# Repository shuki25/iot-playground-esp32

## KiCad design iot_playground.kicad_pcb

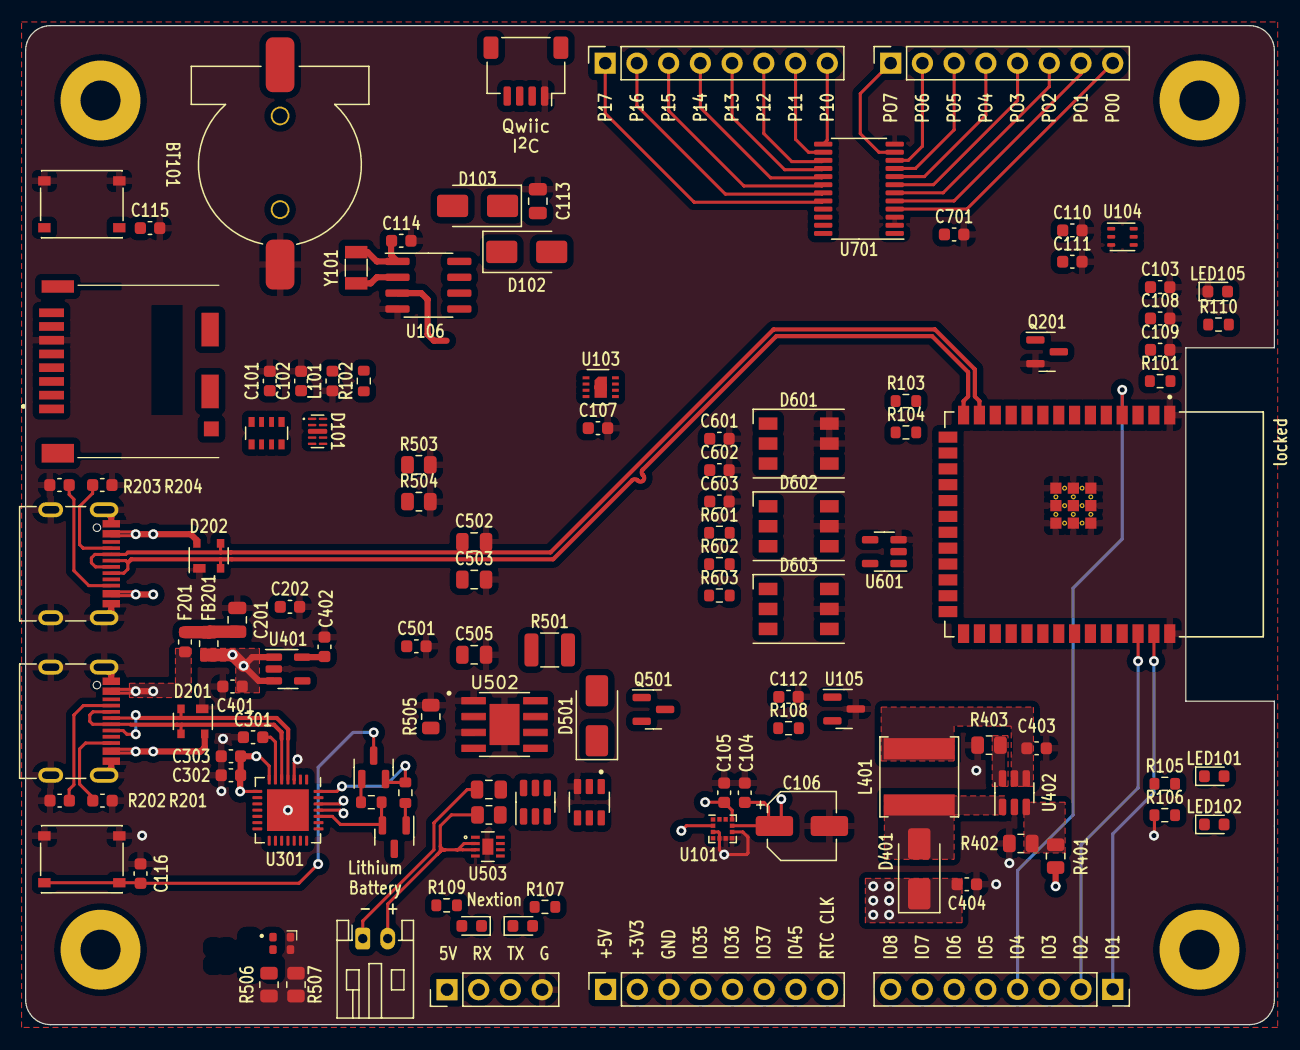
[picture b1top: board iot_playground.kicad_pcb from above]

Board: 4 copper layers, 100.0 x 80.0 mm, 121 parts (0 on the bottom side), 104 nets.

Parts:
BT101: Battery_Cell; BatteryHolder_CR1220
C101, C108: 10uF; C_0603_1608Metric
C102, C104, C105, C107, C109, C110, C112, C115, C116, C202, C301, C303, C601, C602, C603, C701: 100nF; C_0603_1608Metric
C103, C302: 1uF; C_0603_1608Metric
C106: 10uF; CP_Elec_5x5.4
C111, C402: 4.7uF; C_0603_1608Metric
C113, C504, C505: 100nF; C_0805_2012Metric
C114: 15pF; C_0603_1608Metric
C201, C502, C503: 10uF; C_0805_2012Metric
C401, C403, C404, C501: 22uF; C_0603_1608Metric
D101: RClamp0524PATCT; SLP2510P8
D102, D103, D401, D501: D_Schottky; D_SMA
D201, D202: SP0503BAHT; SOT-143
D601, D602, D603: WS2813B; LED_WS2812_PLCC6_5.0x5.0mm_P1.6mm
F201: Polyfuse_Small; Fuse_0603_1608Metric
FB201: FerriteBead_Small; R_0805_2012Metric
H101, H102, H103, H104: MountingHole_Pad; MountingHole_3.2mm_M3_Pad
J101: Micro_SD_Card_Det_Hirose_DM3CS-SF; DM3CS-SF
J102: Conn_01x04; PinHeader_1x04_P2.54mm_Vertical
J103: Conn_01x04; JST_SH_SM04B-SRSS-TB_1x04-1MP_P1.00mm_Horizontal
J104, J106, J701, J702: Conn_01x08; PinSocket_1x08_P2.54mm_Vertical
J105: Conn_01x02; JST_PH_S2B-PH-K_1x02_P2.00mm_Horizontal
J201, J202: USB_C_Receptacle_USB2.0; USB_C_Receptable_918-418K2023S40001
L101: L_Ferrite_Small; L_0603_1608Metric
L401: 6.8 uH; L_6.0x6.0_H4.5
LED101, LED103: BLUE; LED_0603_1608Metric
LED102, LED104: GREEN; LED_0603_1608Metric
LED105: RED; LED_0603_1608Metric
LED501: LED_RAGB; LED-4_1.6x1.6x0.85P
Q201: Q_NMOS_GSD; SOT-23
Q301, Q302: S8050; SOT-23
Q501: Q_PMOS_DGS; SOT-23
Q502: FS8205; SOT95P280X145-6N
R101, R102, R301, R302: 10K; R_0603_1608Metric
R103, R104, R105, R106, R107, R109, R110: 1K; R_0603_1608Metric
R108: 2K7; R_0603_1608Metric
R201, R202, R203, R204: 5K1; C_0603_1608Metric
R401: 7.5K; R_0805_2012Metric
R402, R507: 1K; R_0805_2012Metric
R403: 24K; R_0805_2012Metric
R501: 0.4; R_1210_3225Metric
R502: 100; R_0805_2012Metric
R503: 100K; R_0805_2012Metric
R504, R505, R506: 2K; R_0805_2012Metric
R601, R602, R603: 200; R_0603_1608Metric
RN101: 10K; R_Array_Convex_4x0603
SW101, SW102: SW_SPST; XKB-Connectivity-TS-1187A-B-A-B
U101: LIS2DW12; LGA-12_2x2mm_P0.5mm
U103: SHT30-DIS-B2.5KS; Sensirion_DFN-8-1EP_2.5x2.5mm_P0.5mm_EP1.1x1.7mm
U104: LTR-F216A; Lite-On_LTR-303ALS-01
U105: UHE4913; SOT-23
U106: PCF8563T; SOIC-8_3.9x4.9mm_P1.27mm
U301: CP2102-GMR; QFN-28-1EP_5x5mm_P0.5mm_EP3.35x3.35mm
U401: XC6220B331MR-G; SOT-23-5
U402: MT3608L; SOT-23-6
U501: FS312F-G; SOT-23-6
U502: TP4056; SOP127P600X175-9N
U503: MAX17048; MAX17048G&plus_T10
U601: SN74AHCT1G125DBVR; SOT-23-5
U701: PCA9535PW; TSSOP-24_4.4x7.8mm_P0.65mm
Y101: 32.768k; Crystal_SMD_3215-2Pin_3.2x1.5mm
locked: ESP32-S3-WROOM-1-N8R2; ESP32-S3-WROOM

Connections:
+3V3: C101.1, C102.1, C104.1, C105.1, C106.1, C107.1, C108.1, C109.1, C110.1, C111.1, C112.1, C402.1, C701.1, D102.2 (A), J101.4 (VDD), J103.2, J104.2, R101.2, R102.2, R103.2, R104.2, R105.1, R106.1, R107.1, R108.1, R109.1, R110.1, RN101.5 (R4.2), RN101.6 (R3.2), RN101.7 (R2.2), RN101.8 (R1.2), U101.2 (~CS), U101.9 (Vdd), U101.10 (Vdd_IO), U103.5 (VDD), U104.1 (VDD), U105.2 (VDD), U401.5 (VOUT), U701.24 (VCC), locked.2 (3V3)
+5V: C202.1, C302.1, C303.1, C401.2, C404.1, D401.1 (K), D601.2 (VDD), D602.2 (VDD), D603.2 (VDD), FB201.2, J102.1, J104.1, Q201.1 (G), R401.1, R601.1, R602.1, R603.1, U301.7 (VREGIN), U301.8 (VBUS), U401.1 (VIN), U401.3 (CE), U601.5 (VCC)
+BATT: C503.1, C505.1, J105.2, Q501.3 (D), R502.1, U502.5 (BAT), U503.2 (CELL), U503.3 (VDD)
-BATT: C504.2, J105.1, Q502.1, U501.6 (GND)
/ACC_INT: U101.12 (INT1), locked.34 (IO41)
/ALS_INT: U104.5 (INT), locked.35 (IO42)
/Addressable_LED/LED_IC: D601.4 (DIN), D602.6 (BIN), U601.4
/Battery_Management/VCC: C403.1, C501.1, D501.1 (K), L401.1, Q501.2 (S), U402.4 (EN), U402.5 (IN)
/Battery_Management/VCC_LED: C502.1, LED501.2 (A), R501.2, U502.4 (VCC), U502.8 (CE)
/Battery_Management/~CHRG: R507.1, U502.7 (~CHRG)
/Battery_Management/~STDBY: R506.1, U502.6 (~STDBY)
/CBATT+: BT101.1 (+), D103.2 (A)
/CP2102-ESP32/DTR: Q302.2 (E), R301.2, U301.28 (~DTR)
/CP2102-ESP32/D_N: D201.3 (K), J201.A7 (D-), J201.B7 (D-), U301.5 (D-)
/CP2102-ESP32/D_P: D201.2 (K), J201.A6 (D+), J201.B6 (D+), U301.4 (D+)
/CP2102-ESP32/RTS: Q301.2 (E), R302.2, U301.24 (~RTS)
/EN: C103.1, C115.1, Q301.3 (C), R101.1, SW101.1 (A), locked.3 (EN)
/ESP_RX: LED102.1 (K), U301.26 (TXD), locked.36 (IO44/RXD0)
/ESP_TX: LED101.1 (K), U301.25 (RXD), locked.37 (IO43/TXD0)
/HALL_SNSR: R108.2, U105.1 (VOUT), locked.33 (IO40)
/IO0: C116.1, Q302.3 (C), SW102.1 (A), locked.27 (IO0*)
/IO1: J106.1, locked.39 (IO1)
/IO2: J106.2, locked.38 (IO2)
/IO3: J106.3, locked.15 (IO3*)
/IO4: J106.4, locked.4 (IO4)
/IO5: J106.5, locked.5 (IO5)
/IO6: J106.6, locked.6 (IO6)
/IO7: J106.7, locked.7 (IO7)
/IO8: J106.8, locked.12 (IO8)
/IO35: J104.4, locked.28 (^IO35)
/IO36: J104.5, locked.29 (^IO36)
/IO37: J104.6, locked.30 (^IO37)
/IO45: J104.7, locked.26 (*IO45)
/IO_Expander/P00: J701.8, U701.4 (P00)
/IO_Expander/P01: J701.7, U701.5 (P01)
/IO_Expander/P02: J701.6, U701.6 (P02)
/IO_Expander/P03: J701.5, U701.7 (P03)
/IO_Expander/P04: J701.4, U701.8 (P04)
/IO_Expander/P05: J701.3, U701.9 (P05)
/IO_Expander/P06: J701.2, U701.10 (P06)
/IO_Expander/P07: J701.1, U701.11 (P07)
/IO_Expander/P10: J702.8, U701.13 (P10)
/IO_Expander/P11: J702.7, U701.14 (P11)
/IO_Expander/P12: J702.6, U701.15 (P12)
/IO_Expander/P13: J702.5, U701.16 (P13)
/IO_Expander/P14: J702.4, U701.17 (P14)
/IO_Expander/P15: J702.3, U701.18 (P15)
/IO_Expander/P16: J702.2, U701.19 (P16)
/IO_Expander/P17: J702.1, U701.20 (P17)
/IO_INT: U701.1 (~INT), locked.32 (IO39)
/LED_IC: U601.2, locked.23 (IO21)
/PWR_FLG: Q201.3 (D), locked.8 (IO15/XTAL+)
/RTC_CLKO: J104.8, U106.7 (CLKO)
/RXD1: J102.2, LED104.1 (K), locked.11 (RXD1/IO18)
/SD_DET: J101.9 (DET_B), locked.24 (IO47)
/SD_MISO: D101.1 (K1), J101.7 (DAT0), RN101.4 (R4.1), locked.22 (IO14)
/SD_MOSI: D101.4 (K3), J101.3 (CMD), RN101.2 (R2.1), locked.21 (IO13)
/SD_SCK: D101.2 (K2), J101.5 (CLK), locked.20 (IO12)
/SD_SS: D101.5 (K4), J101.2 (DAT3/CD), RN101.3 (R3.1), locked.19 (IO11)
/TXD1: J102.3, LED103.1 (K), locked.10 (TXD1/IO17)
/USBC-2.0/USB_VCC: D201.4 (K), D202.4 (K), F201.1, J201.A4 (VBUS), J201.A9 (VBUS), J201.B4 (VBUS), J201.B9 (VBUS), J202.A4 (VBUS), J202.A9 (VBUS), J202.B4 (VBUS), J202.B9 (VBUS)
/USB_N: D202.3 (K), J202.A7 (D-), J202.B7 (D-), locked.13 (D-/IO19)
/USB_P: D202.2 (K), J202.A6 (D+), J202.B6 (D+), locked.14 (D+/IO20)
/~ALRT: U503.5 (~ALRT), locked.9 (IO16/XTAL-)
/~BUF_EN: U601.1, locked.31 (IO38)
/~RTC_INT: U106.3 (~INT), locked.25 (IO48)
/~SCL: J103.4, R103.1, U101.4 (SDA/SDI), U103.4 (SCL), U104.4 (SCL), U106.6 (SCL), U503.7 (SCL), U701.22 (SCL), locked.18 (IO10)
/~SDA: J103.3, R104.1, U101.1 (SCL/SPC), U103.1 (SDA), U104.6 (SDA), U106.5 (SDA), U503.8 (SDA), U701.23 (SDA), locked.17 (IO9)
GND: BT101.2 (-), C101.2, C102.2, C103.2, C104.2, C105.2, C106.2, C107.2, C108.2, C109.2, C110.2, C111.2, C112.2, C113.2, C114.1, C115.2, C116.2, C201.2, C202.2, C301.2, C302.2, C303.2, C401.1, C402.2, C403.2, C404.2, C501.2, C502.2, C503.2, C505.2, C601.2, C602.2, C603.2, C701.2, D101.3 (A), D201.1 (A), D202.1 (A), D601.5 (GND), D601.6 (BIN), D602.5 (GND), D603.5 (GND), J101.6 (VSS), J102.4, J103.1, J104.3, J201.A1 (GND), J201.A12 (GND), J201.B1 (GND), J201.B12 (GND), J201.S1 (SHIELD), J202.A1 (GND), J202.A12 (GND), J202.B1 (GND), J202.B12 (GND), J202.S1 (SHIELD), L101.1, LED105.1 (K), Q201.2 (S), Q502.3, R201.1, R202.1, R203.1, R204.1, R402.2, R403.2, R503.2, R504.2, R505.2, SW101.2 (B), SW102.2 (B), U101.3 (SA0/SDO), U101.5 (NC), U101.6 (GND), U101.7 (RES), U101.8 (GND), U103.2 (ADDR), U103.7 (R), U103.8 (VSS), U103.9 (VSS), U104.3 (GND), U105.3 (GND), U106.4 (VSS), U301.3 (GND), U301.29 (GND), U401.2 (GND), U402.2 (GND), U502.1 (TEMP), U502.3 (GND), U502.9 (EP), U503.1 (CTG), U503.4 (GND), U503.6 (QSTRT), U503.9 (EP), U601.3 (GND), U701.2 (A1), U701.3 (A2), U701.12 (GND), U701.21 (A0), locked.1 (GND), locked.40 (GND), locked.41_1 (GND), locked.41_2 (GND), locked.41_3 (GND), locked.41_4 (GND), locked.41_5 (GND), locked.41_6 (GND), locked.41_7 (GND), locked.41_8 (GND), locked.41_9 (GND)
unnamed: C301.1, U301.6 (VDD)
unnamed: C504.1, R502.2, U501.5 (VCC)
unnamed: C201.1, F201.2, FB201.1
unnamed: C113.1, D102.1 (K), D103.1 (K), U106.8 (VDD)
unnamed: D401.2 (A), L401.2, U402.1 (SW)
unnamed: D601.3 (DOUT), D602.4 (DIN), D603.6 (BIN)
unnamed: C601.1, D601.1 (VCC), R601.2
unnamed: D602.3 (DOUT), D603.4 (DIN)
unnamed: C602.1, D602.1 (VCC), R602.2
unnamed: C603.1, D603.1 (VCC), R603.2
unnamed: J101.8 (DAT1), RN101.1 (R1.1)
unnamed: J101.1 (DAT2), R102.1
unnamed: J101.11 (SHIELD), L101.2
unnamed: J201.A5 (CC1), R202.2
unnamed: J201.B5 (CC2), R201.2
unnamed: J202.A5 (CC1), R204.2
unnamed: J202.B5 (CC2), R203.2
unnamed: LED101.2 (A), R105.2
unnamed: LED102.2 (A), R106.2
unnamed: LED103.2 (A), R107.2
unnamed: LED104.2 (A), R109.2
unnamed: LED105.2 (A), R110.2
unnamed: LED501.3 (GK), R506.2
unnamed: LED501.4 (RK), R507.2
unnamed: Q301.1 (B), R301.1
unnamed: Q302.1 (B), R302.1
unnamed: C114.2, U106.1 (OSCI), Y101.1
unnamed: U106.2 (OSCO), Y101.2
unnamed: R401.2, R402.1, U402.3 (FB)
unnamed: R403.1, U402.6 (OC)
unnamed: R504.1, U501.2 (CS)
unnamed: Q502.4, U501.3 (OC)
unnamed: Q502.6, U501.1 (OD)
unnamed: R505.1, U502.2 (PROG)
VBUS: D501.2 (A), Q501.1 (G), R501.1, R503.1

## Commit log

2023-02-08 initial commit
    This reverts commit 54838efe01d276f115d3906eed4c397edf191dfc.
2023-02-08 revert accidentally removed files
2023-02-09 add RTC, humidity and temp sensors
    updated footprint paths
2023-02-09 update LCSC parts and footprints
2023-02-09 initial PCB
2023-02-09 update schematic pdf
2023-02-09 update pcb
2023-02-10 update 3d models
2023-02-13 revise schematics
2023-02-13 update layout
2023-02-13 update pcb layout
2023-02-28 update pcb design
